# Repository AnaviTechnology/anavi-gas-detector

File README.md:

# ANAVI Gas Detector

ANAVI Gas Detector is an open source hardware development board that acts like a WiFi smart gas detector. It features:

* ESP8266 WiFi microcontroller
* DHT22 sensor for temperature and humidity
* Terminal for waterproof DS18B20 1-Wire temperature sensor
* Dedicated slot for I2C OLED display
* Slots for up to 3 plug and play I2C sensors for temperature, barometric pressure, humidity and light
* UART (Universal asynchronous receiver/transmitter) pins for debugging

Open source software for ANAVI Gas Detector written as an Arduino sketch is also available at GitHub](https://github.com/AnaviTechnology/anavi-gas-detector-sw).

# License

The project is released under the [Creative Commons Attribution-ShareAlike 4.0 International (CC BY-SA 4.0)](https://creativecommons.org/licenses/by-sa/4.0/).

Note: This is a human-readable summary of (and not a substitute for) the [license](https://creativecommons.org/licenses/by-sa/4.0/legalcode).

You are free to:

Share — copy and redistribute the material in any medium or format Adapt — remix, transform, and build upon the material for any purpose, even commercially. The licensor cannot revoke these freedoms as long as you follow the license terms. Under the following terms:

Attribution — You must give appropriate credit, provide a link to the license, and indicate if changes were made. You may do so in any reasonable manner, but not in any way that suggests the licensor endorses you or your use. ShareAlike — If you remix, transform, or build upon the material, you must distribute your contributions under the same license as the original. No additional restrictions — You may not apply legal terms or technological measures that legally restrict others from doing anything the license permits. Notices:

You do not have to comply with the license for elements of the material in the public domain or where your use is permitted by an applicable exception or limitation. No warranties are given. The license may not give you all of the permissions necessary for your intended use. For example, other rights such as publicity, privacy, or moral rights may limit how you use the material.

You will have to provide a link to the original creator of the project http://www.anavi.technology on any documentation or website.

Credit can be attributed through a link to the creator website: http://www.anavi.technology

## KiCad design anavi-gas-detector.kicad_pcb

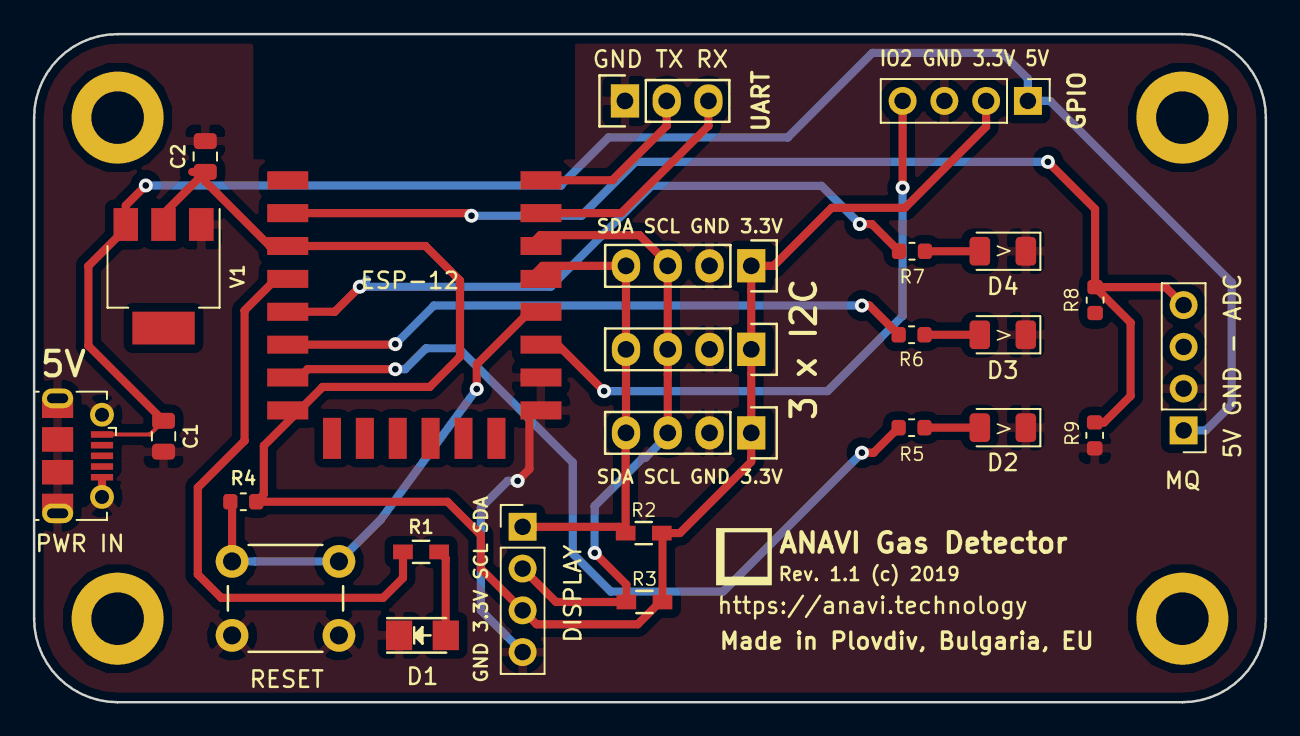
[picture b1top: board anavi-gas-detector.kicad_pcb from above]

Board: 2 copper layers, 74.9 x 40.6 mm, 26 parts (0 on the bottom side), 18 nets.

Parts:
C1, C2: 10uF; C_0805_2012Metric
D1: LED; LED_1206
D2, D3, D4: LED; LED_1206_3216Metric
DISPLAY: Conn_01x04; PinHeader_1x04_P2.54mm_Vertical
ESP-12: ESP-12E; ESP-12E_SMD
GPIO: Conn_01x04; PinHeader_1x04_P2.54mm_Vertical
MQ: Conn_01x04; PinHeader_1x04_P2.54mm_Vertical
P1: CONN_01X03; Pin_Header_Straight_1x03
PWR IN: USB_B_Micro; USB_Micro-B_Molex-105017-0001
R1: 68R; R_0603_HandSoldering
R2, R3: 4,7K; R_0603_HandSoldering
R4: 2K; R_0603_1608Metric
R5, R6, R7: 68R; R_0603_1608Metric
R8: 220K; R_0603_1608Metric
R9: 56K; R_0603_1608Metric
RESET: SW_DIP_x01; SW_PUSH_6mm_h4.3mm
U1, U2, U3: I2C_SENS_1; Pin_Header_Straight_1x04
V1: LD1117S33TR; SOT-223

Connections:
+3V3: C2.1, DISPLAY.3, ESP-12.3, ESP-12.8, GPIO.2, R2.1, R3.1, R4.2, U1.1, U2.1, U3.1, V1.2
+5V: C1.1, GPIO.1, MQ.1, PWR IN.1, V1.3
GND: C1.2, C2.2, D1.1, D2.1, D3.1, D4.1, DISPLAY.4, ESP-12.9, ESP-12.10, GPIO.3, MQ.2, P1.1, PWR IN.5, PWR IN.6, R9.2, RESET.1, U1.2, U2.2, U3.2, V1.1
unnamed: D1.2, R1.2
unnamed: D2.2, R5.2
unnamed: D3.2, R6.2
unnamed: D4.2, R7.2
unnamed: ESP-12.2, MQ.4, R8.2, R9.1
unnamed: ESP-12.4, R1.1
unnamed: ESP-12.5, R7.1
unnamed: ESP-12.6, R6.1
unnamed: ESP-12.7, R5.1
unnamed: ESP-12.11, GPIO.4
unnamed: ESP-12.12, R4.1, RESET.2
unnamed: DISPLAY.1, ESP-12.13, R2.2, U1.4, U2.4, U3.4
unnamed: DISPLAY.2, ESP-12.14, R3.2, U1.3, U2.3, U3.3
unnamed: ESP-12.15, P1.3
unnamed: ESP-12.16, P1.2

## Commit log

2019-04-08 anavi-gas-detector.kicad_pcb: Update labels
    Improve the labels.
2019-04-13 anavi-gas-detector.*: Add voltage dividers
    Add voltage divider to measure accrately the analog
    output from the external gas sensor.
2019-04-15 anavi-gas-detector.kicad_pcb: Rev 1.1
    Update the revision number to 1.1.
2019-07-13 anavi-gas-detector.kicad_pcb: Assembly diagram
    Update assembly instructions.
2019-09-04 doc: Update Gas detector not Thermometer

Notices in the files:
anavi-gas-detector.kicad_pcb:
Rev. 1.1 (c) 2019
